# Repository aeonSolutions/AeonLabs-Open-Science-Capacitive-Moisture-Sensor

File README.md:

[ ](https://discord.gg/hw3j3RwfJf)

**Unique Visits** 

</p>

[PCB-Prototyping-Catalogue](https://github.com/aeonSolutions/PCB-Prototyping-Catalogue)  >>  [Laboratory Automation](https://github.com/aeonSolutions/PCB-Prototyping-Catalogue/tree/main/Laboratory%20Automation) >> Purposely designed sensors  >> Capacitive-Moisture and Temperature  made for 100 mm height laboratory specimens 

<p align="right">
 <a href="https://github-com.translate.goog/aeonSolutions/PCB-Prototyping-Catalogue/tree/main?_x_tr_sl=en&_x_tr_tl=pt&_x_tr_hl=en&_x_tr_pto=wapp">Change Language</a> <br>
Last update: 13-04-2024
</p>

# Capacitive Moisture and Temperature Sensor
<sup>   **status: <a href="https://en.wikipedia.org/wiki/Minimum_viable_product">M.V.P.</a>** NOW SELLING on <a href="https://www.tindie.com/stores/aeonlabs/">Tindie.com</a>  </sup> <br>

### For Laboratory Specimens with 100mm height
This is a capacitive moisture and temperature sensor purposely made for laboratory specimens with 100mm height. 

<p align="center">
      <br>
     
</p>

<p align="center">
<strong> <a href="https://aeonsolutions.github.io/sponsor/capacitive_sensor_probe_50mm/">Interactive view of the PCB Layout</a> </strong> &nbsp;
  <strong> <a href="https://aeonsolutions.github.io/sponsor/capacitive_sensor_probe_50mm/circuit_schematic.html">Interactive view of the circuit schematic</a> </strong> <br>
 <sup>Click to view the latest revision</sup>
</p>

### For Laboratory Specimens with 50mm height
This is a capacitive moisture and temperature sensor purposely made for laboratory specimens with 50mm height. 

<p align="center">
      <br>
     
</p>

<p align="center">
<strong> <a href="https://aeonsolutions.github.io/sponsor/capacitive_sensor_probe_50mm/">Interactive view of the PCB Layout</a> </strong> &nbsp;
  <strong> <a href="https://aeonsolutions.github.io/sponsor/capacitive_sensor_probe_50mm/circuit_schematic.html">Interactive view of the circuit schematic</a> </strong> <br>
 <sup>Click to view the latest revision</sup>
</p>

## CE Ready Logo
This hardware is ready to get a CE marking. To learn more about this marking goto to [Wikipedia here](https://en.wikipedia.org/wiki/CE_marking).

<br>
<br />

**Hire AeonLabs** <br>
If you like my work here and are looking to design and deploy your own smart device find [here](https://github.com/aeonSolutions/PCB-Prototyping-Catalogue/wiki/How-to-Hire-AeonLabs) how to hire me. 

<br />

## Author

You can get in touch with me on my LinkedIn Profile:

#### Miguel Tomas

You can also follow my GitHub Profile to stay updated about my latest projects: 

<br>

### Be supportive of my dedication and work towards technology education and buy me a cup of coffee
The PCB design Files I provide here for anyone to use are free. If you like this Smart Device or use it, please consider buying me a cup of coffee, a slice of pizza or a book to help me study, eat and think new PCB design files.

<p align="center">
    
</p>

### Make a donation on PayPal
Make a donation on PayPal and get a TAX refund*.

<p align="center">
    
</p>

### Support all these open hardware projects and become a GitHub sponsor  
Did you like any of my PCB KiCad Designs? Help and Support my open work to all by becoming a GitHub sponsor.

<p align="center">

</p>

# 

### License

Before proceeding to download any of AeonLabs software solutions for open-source development and/or PCB hardware electronics development make sure you are choosing the right license for your project. See [AeonLabs Solutions for Open Hardware & Source Development](https://github.com/aeonSolutions/PCB-Prototyping-Catalogue/wiki/AeonLabs-Solutions-for-Open-Hardware-&-Source-Development) for more information.

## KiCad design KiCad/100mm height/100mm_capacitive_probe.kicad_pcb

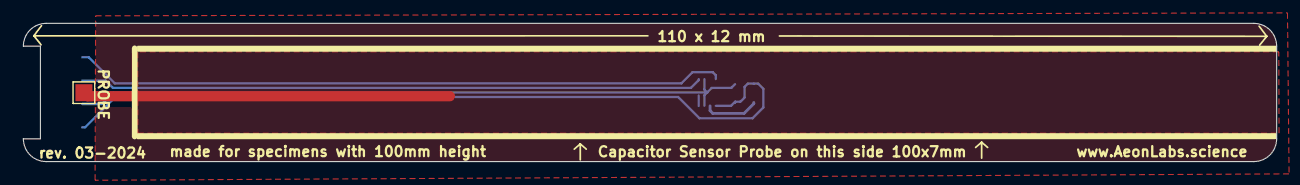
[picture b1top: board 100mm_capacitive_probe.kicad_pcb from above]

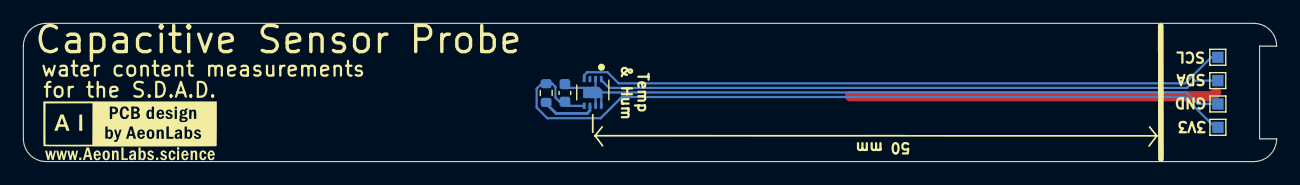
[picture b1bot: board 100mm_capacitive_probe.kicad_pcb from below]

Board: 2 copper layers, 110.1 x 12.1 mm, 8 parts (7 on the bottom side), 5 nets.

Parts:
IMUC1: 100nF; C_0603_1608Metric
J1: Conn_01x01_Pin; TestPoint_Pad_1.5x1.5mm
J3, J4, J5, J6: Conn_01x01_Pin; TestPoint_Pad_1.0x1.0mm
RSTR1: 10K; R_0603_1608Metric
SH1: SHT31-DIS; Sensirion_DFN-8-1EP_2.5x2.5mm_P0.5mm_EP1.1x1.7mm

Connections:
3V3: IMUC1.2, J5.1, RSTR1.1, SH1.5 (VDD)
GND: IMUC1.1, J6.1, SH1.2 (ADDR), SH1.7 (R), SH1.8 (VSS), SH1.9 (VSS)
GPIO8_I2C_SDA: J3.1, SH1.1 (SDA)
GPIO9_I2C_SCL: J4.1, SH1.4 (SCL)
unnamed: RSTR1.2, SH1.6 (~RESET)
